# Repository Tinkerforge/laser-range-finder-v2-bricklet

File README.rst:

Laser Range Finder Bricklet 2.0
===============================

This repository contains the firmware source code and the hardware design
files. The documentation generator configs can be found at
https://github.com/Tinkerforge/generators

Repository Content
------------------

software/:
 * examples/: Examples for all supported languages
 * build/: Compiled files
 * src/: Source code of firmware
 * Makefile: Makefile to build project

hardware/:
 * Contains KiCad project files and additionally schematics as PDF

datasheets/:
 * Contains datasheets for sensors and complex ICs that are used

Hardware
--------

The hardware is designed with the open source EDA Suite KiCad
(http://www.kicad.org). Before you are able to open the files,
you have to install the Tinkerforge kicad-libraries
(https://github.com/Tinkerforge/kicad-libraries). You can either clone
them directly in hardware/ or clone them in a separate folder and
symlink them into hardware/
(ln -s kicad_path/kicad-libraries project_path/hardware). After that you
can open the .pro file in hardware/ with KiCad and from there view and
modify the schematics and the PCB layout.

Software
--------

If you want to do your own Brick/Bricklet firmware development we highly
recommend that you use our build environment setup script and read the
tutorial (https://www.tinkerforge.com/en/doc/Tutorials/Tutorial_Build_Environment/Tutorial.html).

To compile the C code we recommend you to install the newest GNU Arm Embedded
Toolchain (https://launchpad.net/gcc-arm-embedded/+download).
You also need to install bricklib2 (https://github.com/Tinkerforge/bricklib2).

You can either clone it directly in software/src/ or clone it in a
separate folder and symlink it into software/src/
(ln -s bricklib_path/bricklib2 project_path/software/src/). Finally make sure to
have CMake installed (http://www.cmake.org/cmake/resources/software.html).

After that you can build the firmware by invoking make in software/.
The firmware (.zbin) can then be found in software/build/ and uploaded
with brickv (click button "Flashing" on start screen).

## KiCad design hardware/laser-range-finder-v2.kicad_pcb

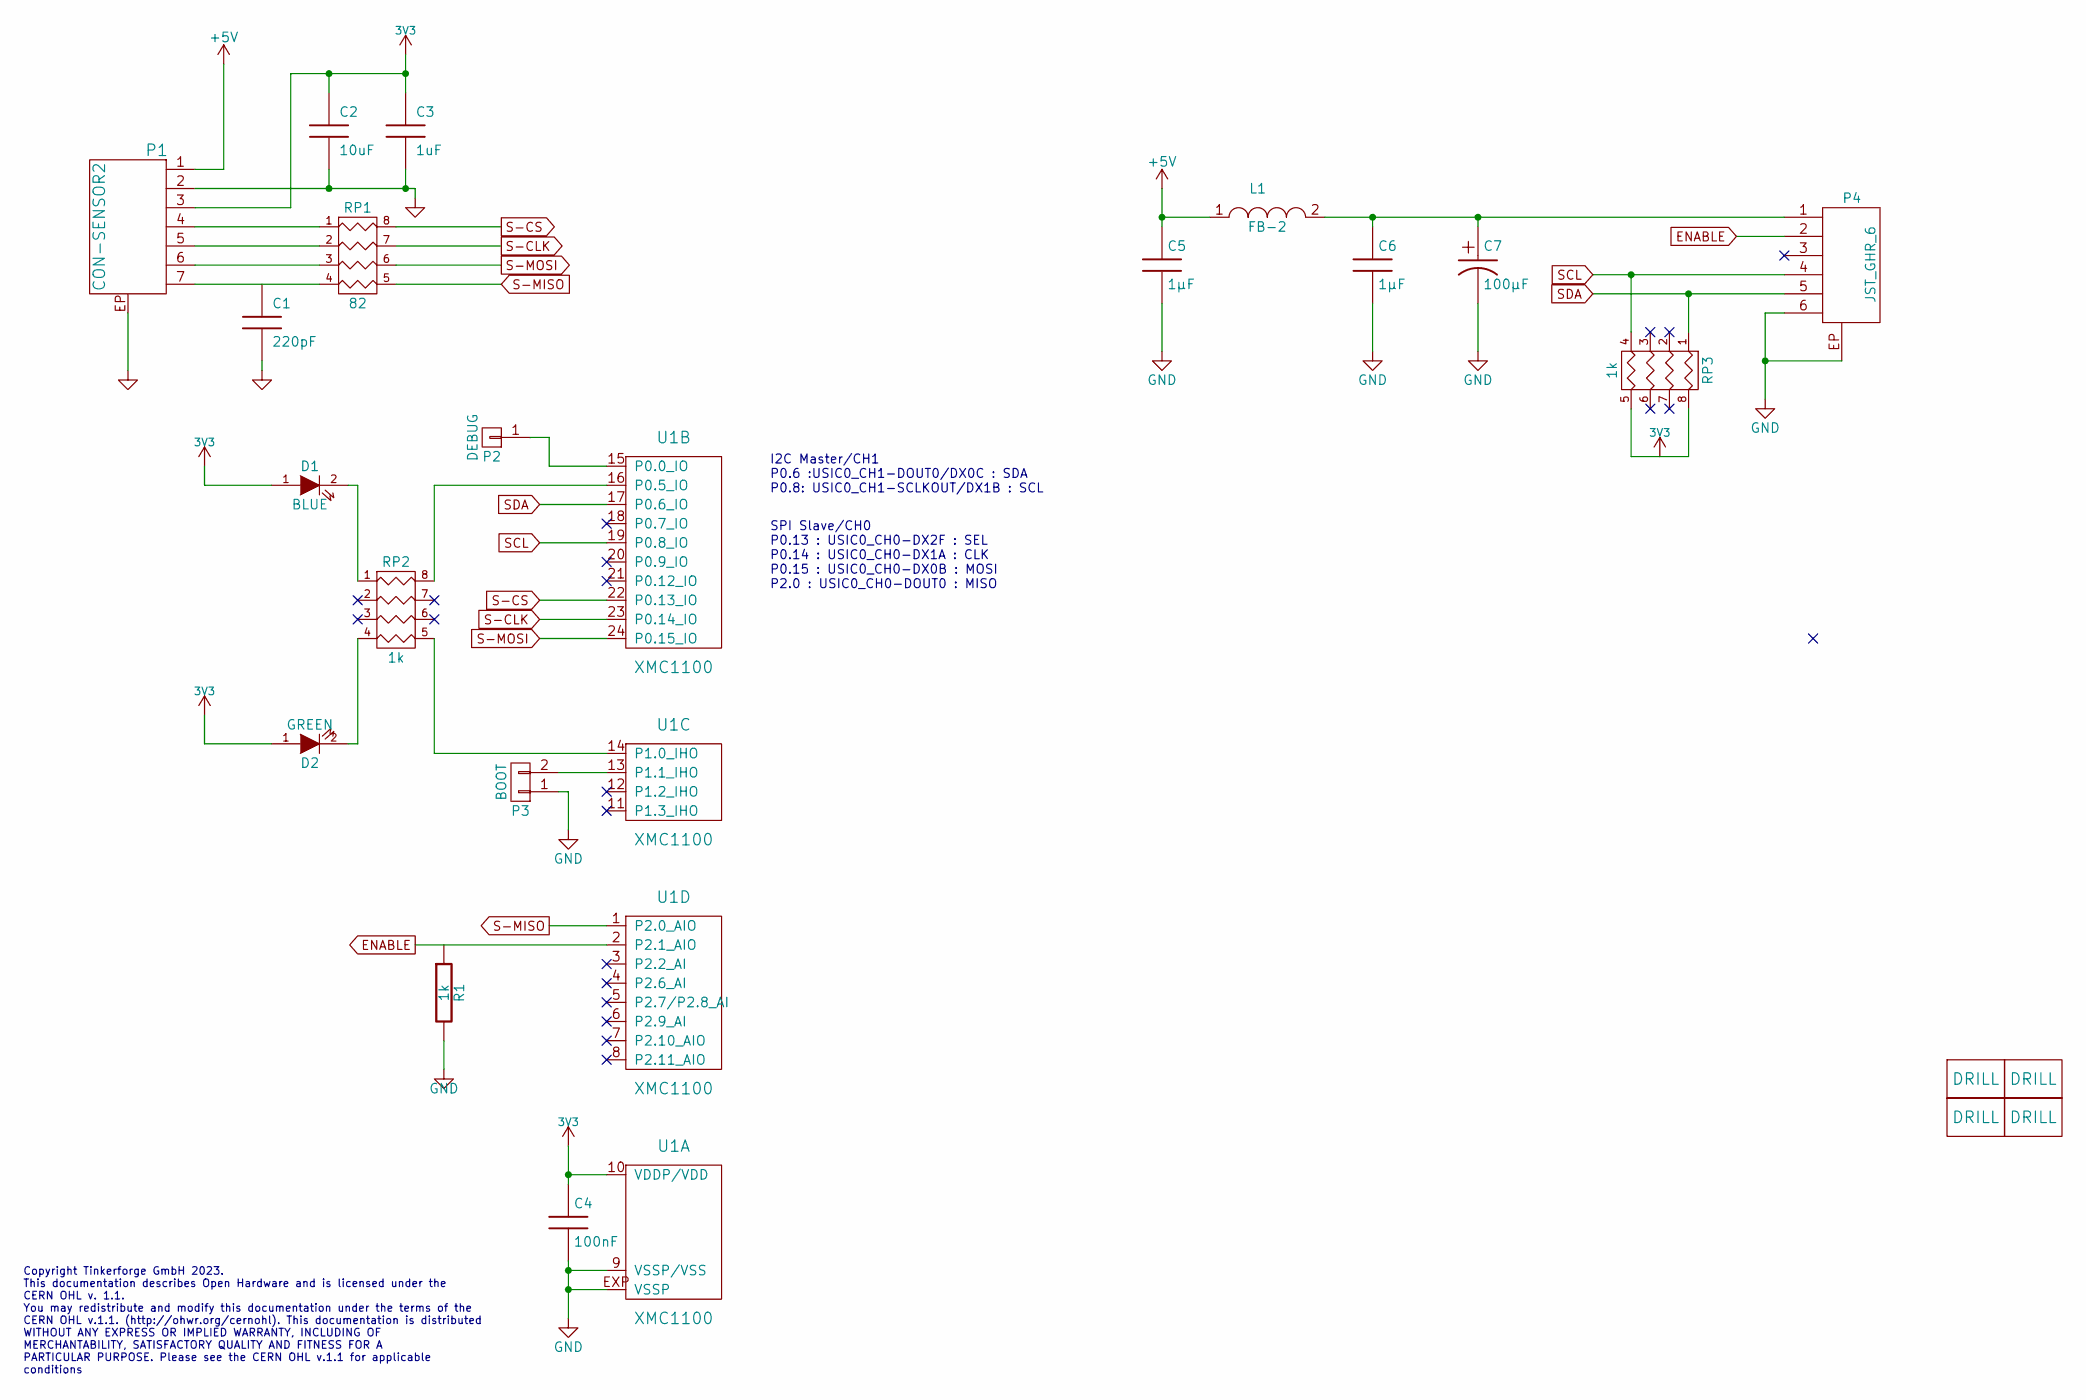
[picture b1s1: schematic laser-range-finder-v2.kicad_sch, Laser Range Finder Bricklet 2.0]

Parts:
C1: 220pF; C0402E
C2: 10uF; C0805E
C3: 1uF; C0603F
C4: 100nF; C0603F
C5, C6: 1µF; C0603E
C7: 100µF; 3528-21
D1: BLUE; D0603F
D2: GREEN; D0603F
L1: FB-2; R0603E
P1: CON-SENSOR2
P2: DEBUG; DEBUG_PAD
P3: BOOT; SolderJumper
P4: JST_GHR_6
R1: 1k; R0603E
RP1: 82; 4X0402
RP2, RP3: 1k; 4X0603
U1: XMC1100; QFN24-4x4mm-0.5mm
U2, U3, U4, U5: DRILL; DRILL_NP

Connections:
3V3: C2.1, C3.1, C4.1, D1.1 (A), D2.1 (A), P1.3, RP3.5 (R4), RP3.8 (R1), U1.10 (VDDP/VDD)
+5V: C5.1, L1.1, P1.1
ENABLE: P4.2, R1.1, U1.2 (P2.1_AIO)
GND: C1.2, C2.2, C3.2, C4.2, C5.2, C6.2, C7.2, P1.2, P1.EP, P3.1, P4.6, P4.EP, R1.2, U1.9 (VSSP/VSS), U1.EXP (VSSP)
unnamed: C6.1, C7.1, L1.2, P4.1
unnamed: D1.2 (K), RP2.1
unnamed: D2.2 (K), RP2.4
unnamed: P1.4, RP1.1
unnamed: P1.5, RP1.2
unnamed: P1.6, RP1.3
unnamed: P2.1, U1.15 (P0.0_IO)
unnamed: P3.2, U1.13 (P1.1_IHO)
unnamed: RP2.5 (R4), U1.14 (P1.0_IHO)
unnamed: RP2.8 (R1), U1.16 (P0.5_IO)
S-CLK: RP1.7 (R2), U1.23 (P0.14_IO)
S-CS: RP1.8 (R1), U1.22 (P0.13_IO)
S-MISO: RP1.5 (R4), U1.1 (P2.0_AIO)
S-MOSI: RP1.6 (R3), U1.24 (P0.15_IO)
SCL: P4.4, RP3.4, U1.19 (P0.8_IO)
SDA: P4.5, RP3.1, U1.17 (P0.6_IO)

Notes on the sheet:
Copyright Tinkerforge GmbH 2023. This documentation describes Open Hardware and is licensed under the CERN OHL v. 1.1. You may redistribute and modify this documentation under the terms of the CERN OHL v.1.1. (http://ohwr.org/cernohl). This documentation is distributed WITHOUT ANY EXPRESS OR IMPLIE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
I2C Master/CH1 P0.6 :USIC0_CH1-DOUT0/DX0C : SDA P0.8: USIC0_CH1-SCLKOUT/DX1B : SCL
SPI Slave/CH0 P0.13 : USIC0_CH0-DX2F : SEL P0.14 : USIC0_CH0-DX1A : CLK P0.15 : USIC0_CH0-DX0B : MOSI P2.0 : USIC0_CH0-DOUT0 : MISO

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
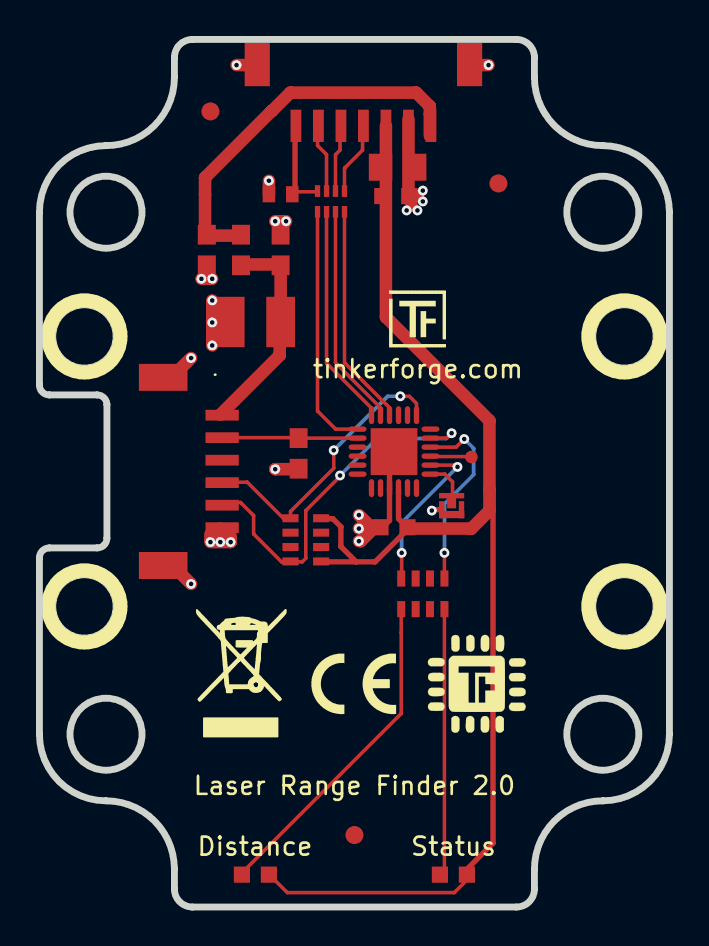
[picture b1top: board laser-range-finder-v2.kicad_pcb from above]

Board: 2 copper layers, 35.0 x 48.2 mm, 28 parts (0 on the bottom side), 21 nets.

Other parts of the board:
Fiducial_Mark: VAL**; Fiducial_Mark
Fiducial_Mark#2, Fiducial_Mark#3: VAL**; Fiducial_Mark
VAL: WEEE_7mm
VAL#2: CE_5mm

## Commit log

2018-07-18 Add datasheets
2018-07-31 Fix readme
2018-07-31 Add .gitignore
2018-08-08 initial schematic and board checkin
2018-08-08 changed pcb design
2018-08-10 added datasheets
2018-08-10 add new datasheet
2018-09-04 add missing sym table
2018-09-04 some minor improvements
2018-09-18 changed footprints C2, C3, RP1
2018-10-22 Rename datasheets
2019-01-17 small things
2019-01-17 add fiducials, fix drc bugs, optimize routing
2019-02-22 changed processor to XMC1100
2019-05-07 Add Laser Range Finder Bricklet firmware
2019-05-08 Turn logging off
2019-05-08 Add support for distance led
2019-05-08 Properly turn laser off if disabled
2019-05-08 Add configuration parameter range check
2019-05-09 add schematic
2019-05-09 Add missing switch cases for distance led config
2019-05-13 fix file names
2019-05-15 add lidar light sensor to 3d model
2019-05-15 add 3d model
2019-05-20 Release Bricklet
2019-05-29 Increase version for new release (changes in bricklib2)
2019-05-29 Add rev to changelog
2019-11-15 Don't allow offsets that would overflow the distance calculation.
2020-04-02 Add examples.
2020-04-07 Fix signedness of examples.
2020-04-07 examples: rust: Always block when calling bindings functions.
2020-08-19 Add uc examples.
2020-08-25 uc: Fix whitespace
2020-08-27 uc: Fix warnings.
2020-08-31 uc: Use fixed-with placeholders in format strings.
2020-09-02 uc: Add example driver note.
2020-09-22 In lidar lite v3 the data is invalid if distance is 1cm
    In the older versions it was invald if the MSB is set.
2020-09-22 Disable quick termination by default and write configuration on startup
2020-09-22 Add ref for 2.0.2
2021-10-25 Update KiCad link
    https://www.kicad.org/blog/2021/10/Avoid-links-to-former-kicad-domain/
2022-04-19 examples: uc: Rename TF_HalContext to TF_HAL.
2022-04-27 uc: Adapt to bindings changes
2022-05-10 go: Fix format string
2022-07-06 Add license files.
2023-01-27 fix schematic
2023-01-27 Data Cleanup

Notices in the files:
hardware/laser-range-finder-v2.kicad_pcb:
Licensed under CERN OHL v.1.1
Copyright (©) 2023, T.Schneidermann
